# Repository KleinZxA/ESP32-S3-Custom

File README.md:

# ESP32-S3-Custom
A Custom ESP32-S3 Dev Board

Note: This is my first time Designing a PCB, I just learned from YT Tutorials and Guides. So some things might be wrong feel free to edit it to your liking in KiCad =)

Btw this is a 2-Layer PCB

## PCB View

## Front 2D & 3D View

## Back 2D & 3D View

# Dimensions

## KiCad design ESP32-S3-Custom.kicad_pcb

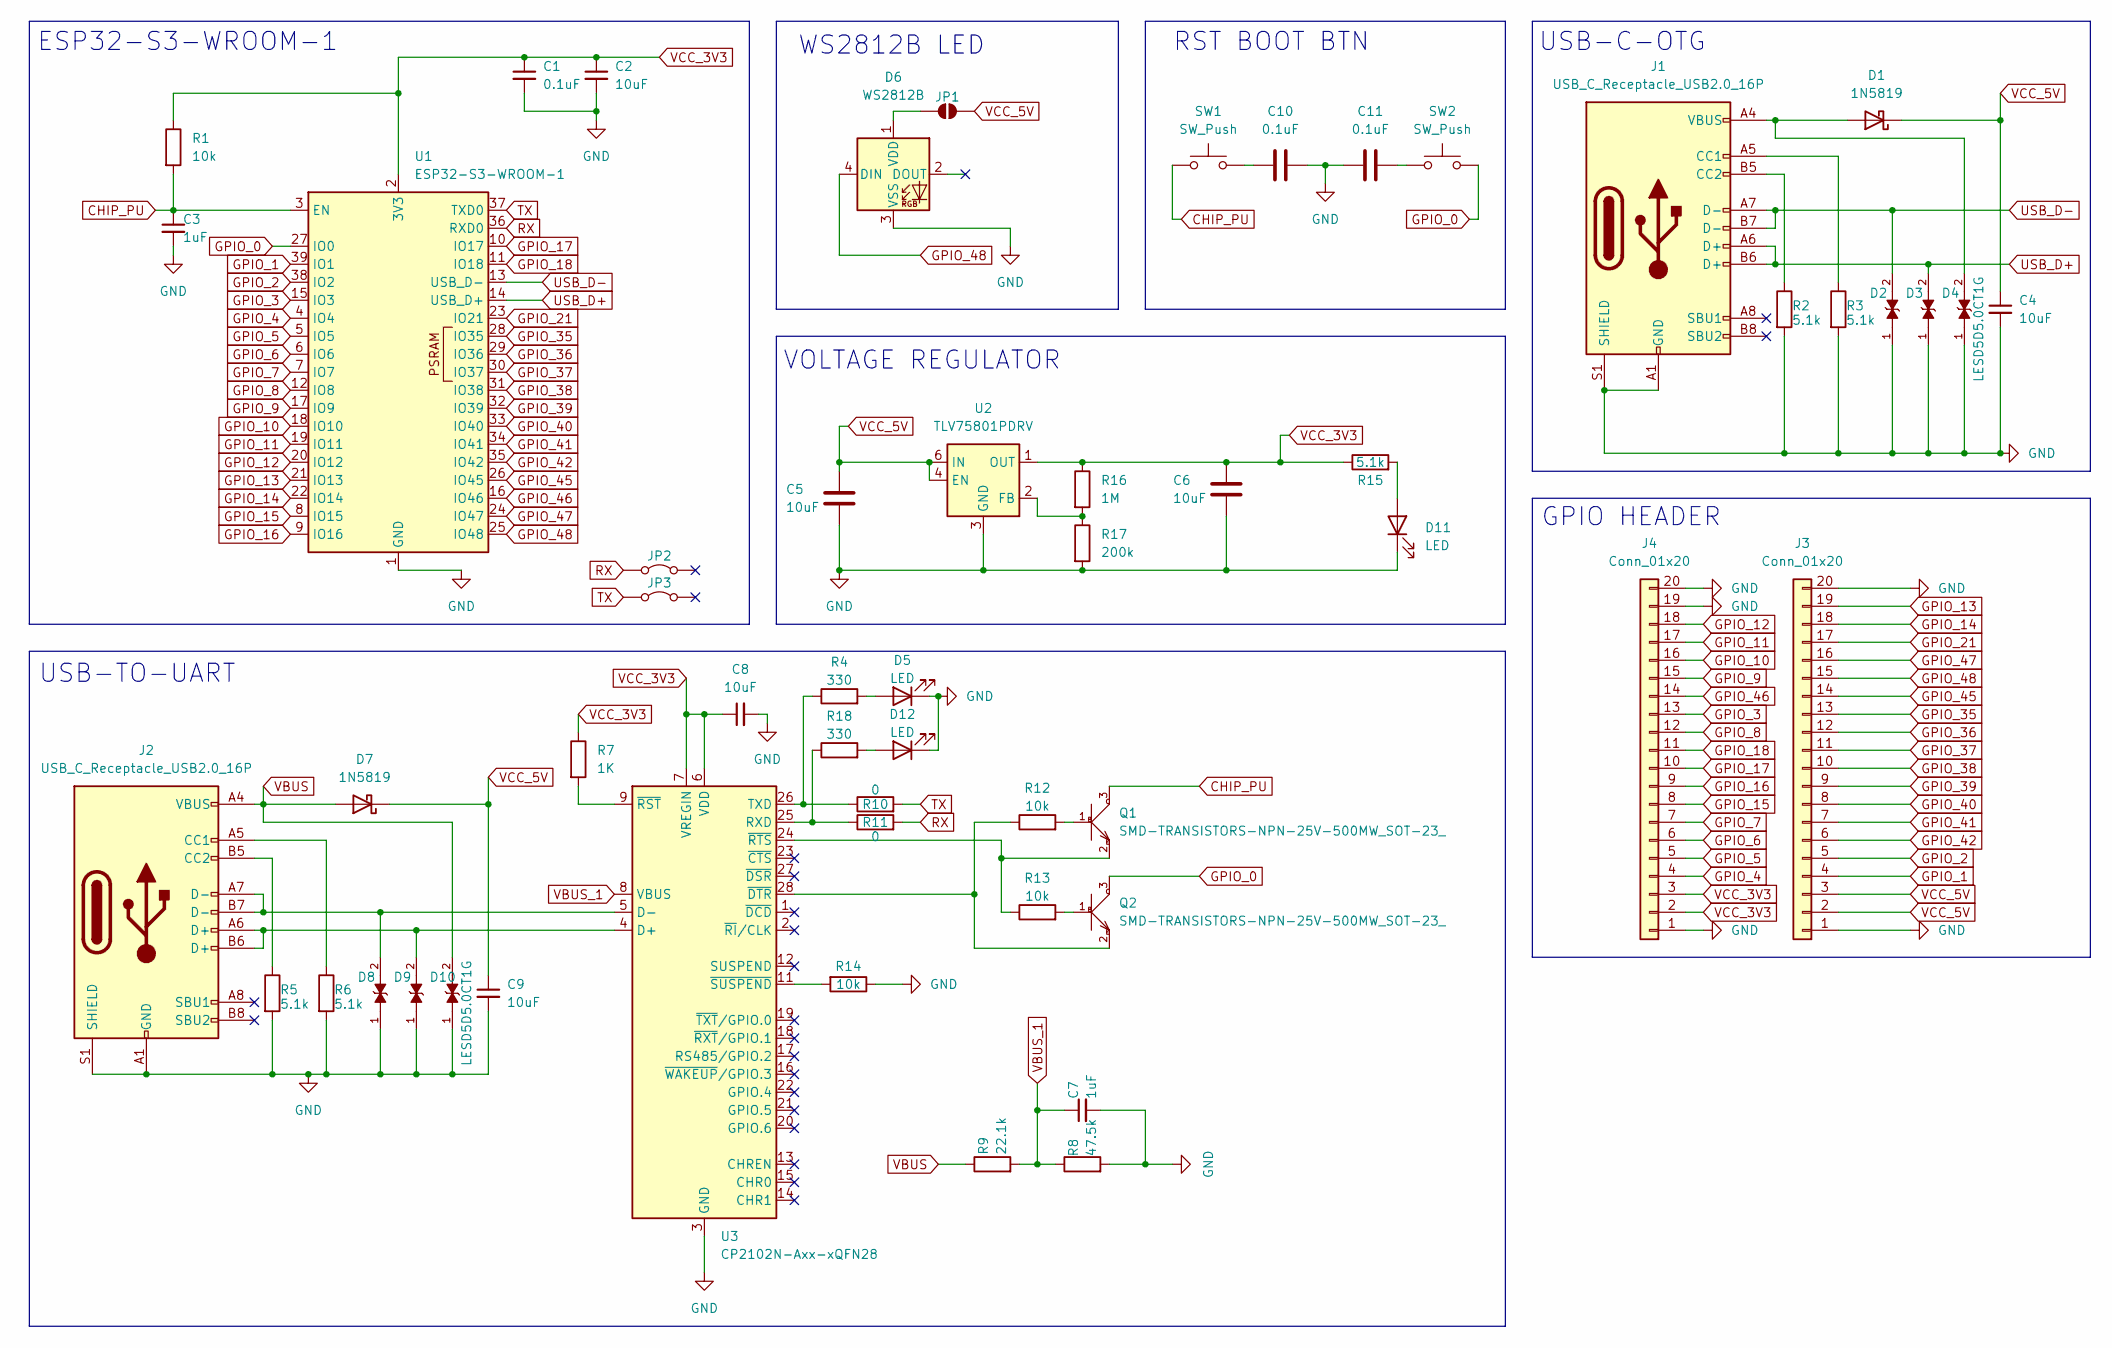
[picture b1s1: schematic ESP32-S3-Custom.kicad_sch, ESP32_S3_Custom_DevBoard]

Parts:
C1, C10, C11: 0.1uF; C_0201_0603Metric
C2, C4, C5, C6, C8, C9: 10uF; C_0201_0603Metric
C3, C7: 1uF; C_0201_0603Metric
D1, D7: 1N5819; D_0603_1608Metric
D2, D3, D4, D8, D9, D10: LESD5D5.0CT1G; TVS_LESD5D5.0CT1G; PARTREV O
D5, D11, D12: LED; LED_0201_0603Metric
D6: WS2812B; LED_WS2812B_PLCC4_5.0x5.0mm_P3.2mm
J1, J2: USB_C_Receptacle_USB2.0_16P; USB_C_Receptacle_GCT_USB4105-xx-A_16P_TopMnt_Horizontal
J3, J4: Conn_01x20; PinHeader_1x20_P2.54mm_Vertical
JP1: SolderJumper_2_Open; SolderJumper-2_P1.3mm_Open_TrianglePad1.0x1.5mm
JP2, JP3: Jumper_2_Bridged; SolderWirePad_1x01_SMD_1x2mm
Q1, Q2: SMD-TRANSISTORS-NPN-25V-500MW_SOT-23_; SOT-23; MPN S8050
R1, R12, R13, R14: 10k; R_0201_0603Metric
R2, R3, R5, R6, R15: 5.1k; R_0201_0603Metric
R4, R18: 330; R_0201_0603Metric
R7: 1K; R_0201_0603Metric
R8: 47.5k; R_0201_0603Metric
R9: 22.1k; R_0201_0603Metric
R10, R11: 0; R_0201_0603Metric
R16: 1M; R_0201_0603Metric
R17: 200k; R_0201_0603Metric
SW1, SW2: SW_Push; SW_SPST_B3U-1000P
U1: ESP32-S3-WROOM-1
U2: TLV75801PDRV; WSON-6-1EP_2x2mm_P0.65mm_EP1x1.6mm
U3: CP2102N-Axx-xQFN28; QFN-28-1EP_5x5mm_P0.5mm_EP3.35x3.35mm

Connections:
CHIP_PU: C3.1, Q1.3, R1.2, SW1.1, U1.3 (EN)
GND: C1.2, C2.2, C3.2, C4.2, C5.2, C6.2, C7.2, C8.2, C9.2, C10.1, C11.2, D2.1, D3.1, D4.1, D5.1 (K), D6.3 (VSS), D8.1, D9.1, D10.1, D11.1 (K), D12.1 (K), J1.A1 (GND), J1.A12 (GND), J1.B1 (GND), J1.B12 (GND), J1.S1 (SHIELD), J2.A1 (GND), J2.A12 (GND), J2.B1 (GND), J2.B12 (GND), J2.S1 (SHIELD), J3.1, J3.20, J4.1, J4.19, J4.20, R2.2, R3.2, R5.2, R6.2, R8.2, R14.1, R17.2, U1.1 (GND), U1.40 (GND), U1.41 (GND), U2.3 (GND), U2.7 (GND), U3.3 (GND), U3.29 (GND)
GPIO_0: Q2.3, SW2.2, U1.27 (IO0)
GPIO_1: J3.4, U1.39 (IO1)
GPIO_2: J3.5, U1.38 (IO2)
GPIO_3: J4.13, U1.15 (IO3)
GPIO_4: J4.4, U1.4 (IO4)
GPIO_5: J4.5, U1.5 (IO5)
GPIO_6: J4.6, U1.6 (IO6)
GPIO_7: J4.7, U1.7 (IO7)
GPIO_8: J4.12, U1.12 (IO8)
GPIO_9: J4.15, U1.17 (IO9)
GPIO_10: J4.16, U1.18 (IO10)
GPIO_11: J4.17, U1.19 (IO11)
GPIO_12: J4.18, U1.20 (IO12)
GPIO_13: J3.19, U1.21 (IO13)
GPIO_14: J3.18, U1.22 (IO14)
GPIO_15: J4.8, U1.8 (IO15)
GPIO_16: J4.9, U1.9 (IO16)
GPIO_17: J4.10, U1.10 (IO17)
GPIO_18: J4.11, U1.11 (IO18)
GPIO_21: J3.17, U1.23 (IO21)
GPIO_35: J3.13, U1.28 (IO35)
GPIO_36: J3.12, U1.29 (IO36)
GPIO_37: J3.11, U1.30 (IO37)
GPIO_38: J3.10, U1.31 (IO38)
GPIO_39: J3.9, U1.32 (IO39)
GPIO_40: J3.8, U1.33 (IO40)
GPIO_41: J3.7, U1.34 (IO41)
GPIO_42: J3.6, U1.35 (IO42)
GPIO_45: J3.14, U1.26 (IO45)
GPIO_46: J4.14, U1.16 (IO46)
GPIO_47: J3.16, U1.24 (IO47)
GPIO_48: D6.4 (DIN), J3.15, U1.25 (IO48)
unnamed: C10.2, SW1.2
unnamed: C11.1, SW2.1
unnamed: D1.2 (A), D4.2, J1.A4 (VBUS), J1.A9 (VBUS), J1.B4 (VBUS), J1.B9 (VBUS)
unnamed: D5.2 (A), R4.2
unnamed: D6.1 (VDD), JP1.1 (A)
unnamed: D11.2 (A), R15.2
unnamed: D12.2 (A), R18.2
unnamed: J1.A5 (CC1), R3.1
unnamed: J1.B5 (CC2), R2.1
unnamed: J2.A5 (CC1), R6.1
unnamed: J2.B5 (CC2), R5.1
unnamed: Q1.1, R12.2
unnamed: Q2.1, R13.2
unnamed: R16.2, R17.1, U2.2 (FB)
unnamed: D9.2, J2.A6 (D+), J2.B6 (D+), U3.4 (D+)
unnamed: D8.2, J2.A7 (D-), J2.B7 (D-), U3.5 (D-)
unnamed: R11.1, R18.1, U3.25 (RXD)
unnamed: R4.1, R10.1, U3.26 (TXD)
unnamed: Q2.2, R12.1, U3.28 (~DTR)
unnamed: R7.2, U3.9 (~RST)
unnamed: Q1.2, R13.1, U3.24 (~RTS)
unnamed: R14.2, U3.11 (~SUSPEND)
RX: JP2.1 (A), R11.2, U1.36 (RXD0)
TX: JP3.1 (A), R10.2, U1.37 (TXD0)
USB_D+: D3.2, J1.A6 (D+), J1.B6 (D+), U1.14 (USB_D+)
USB_D-: D2.2, J1.A7 (D-), J1.B7 (D-), U1.13 (USB_D-)
VBUS: D7.2 (A), D10.2, J2.A4 (VBUS), J2.A9 (VBUS), J2.B4 (VBUS), J2.B9 (VBUS), R9.1
VBUS_1: C7.1, R8.1, R9.2, U3.8 (VBUS)
VCC_3V3: C1.1, C2.1, C6.1, C8.1, J4.2, J4.3, R1.1, R7.1, R15.1, R16.1, U1.2 (3V3), U2.1 (OUT), U3.6 (VDD), U3.7 (VREGIN)
VCC_5V: C4.1, C5.1, C9.1, D1.1 (K), D7.1 (K), J3.2, J3.3, JP1.2 (B), U2.4 (EN), U2.6 (IN)

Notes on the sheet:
WS2812B LED
VOLTAGE REGULATOR
ESP32-S3-WROOM-1
RST BOOT BTN
USB-TO-UART
GPIO HEADER
USB-C-OTG

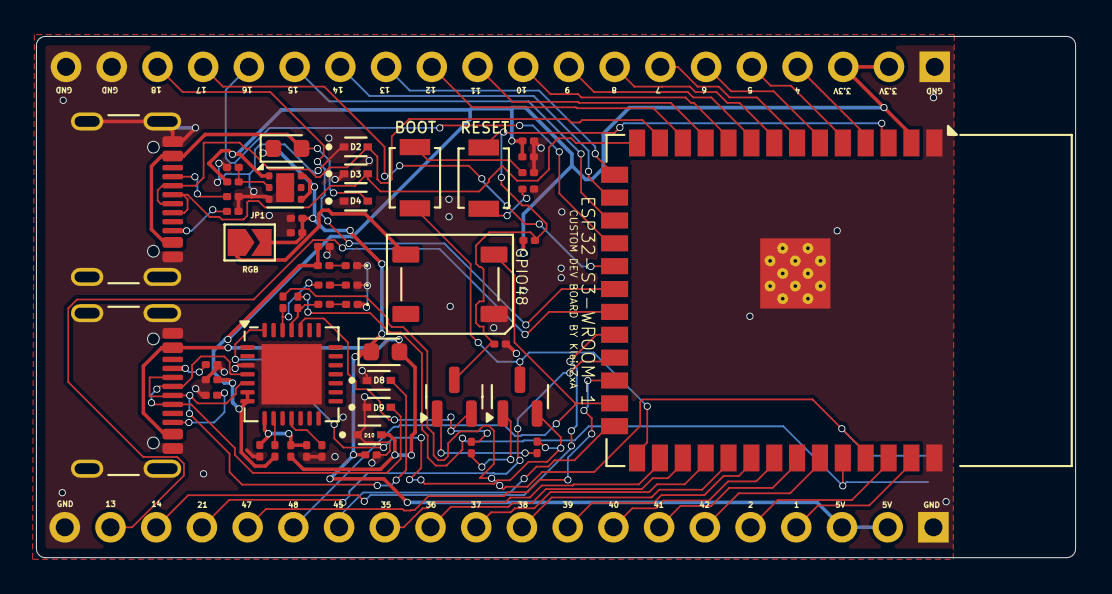
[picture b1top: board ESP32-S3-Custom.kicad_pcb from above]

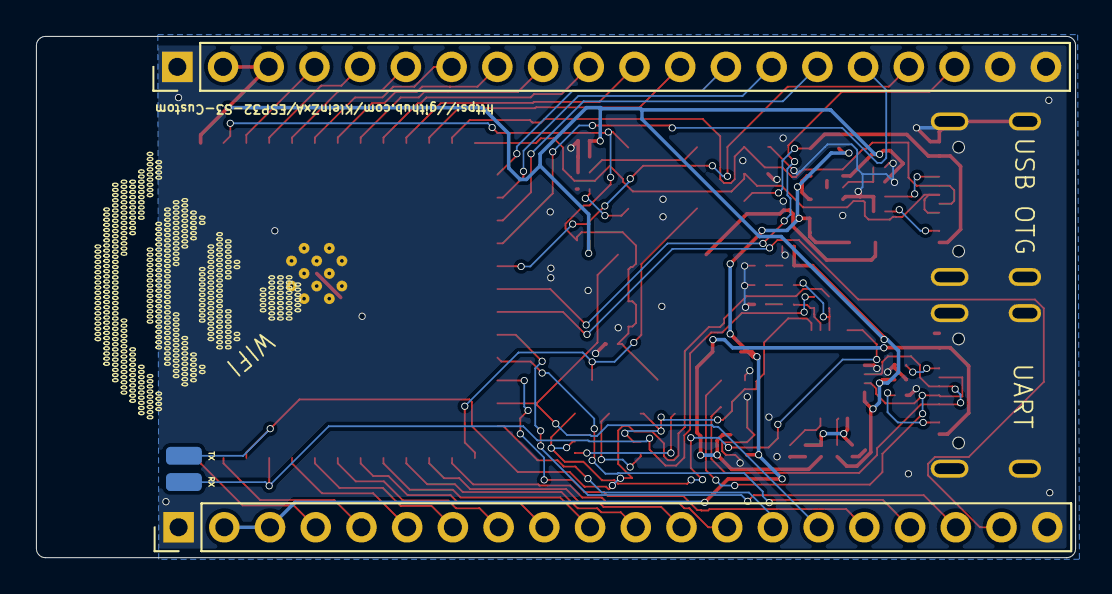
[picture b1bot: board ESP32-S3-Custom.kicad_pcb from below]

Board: 2 copper layers, 57.7 x 29.0 mm, 55 parts (4 on the bottom side), 64 nets.

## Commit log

2025-07-05 Made to 4mm Via Diameter
